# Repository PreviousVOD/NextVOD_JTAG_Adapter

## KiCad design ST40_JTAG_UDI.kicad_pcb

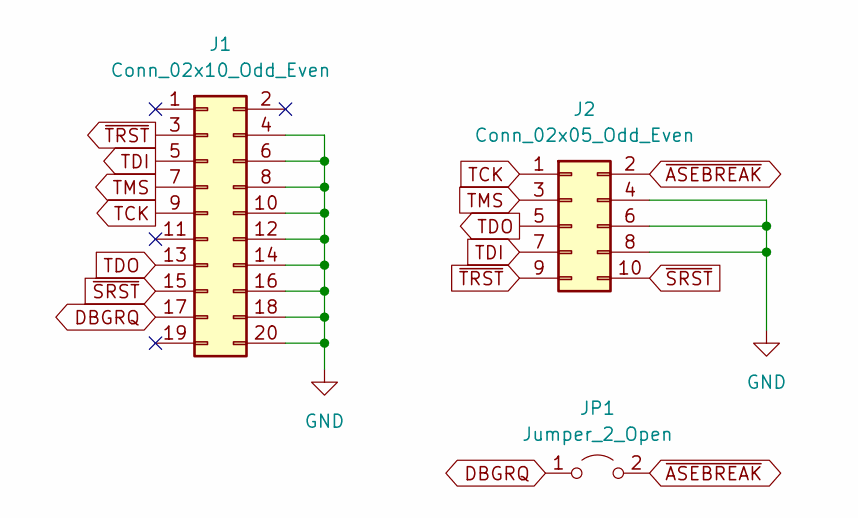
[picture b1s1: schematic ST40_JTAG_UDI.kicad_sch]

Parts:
J1: Conn_02x10_Odd_Even; PinHeader_2x10_P2.54mm_Vertical
J2: Conn_02x05_Odd_Even; PinHeader_2x05_P1.27mm_Vertical
JP1: Jumper_2_Open; SolderJumper-2_P1.3mm_Open_TrianglePad1.0x1.5mm

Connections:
DBGRQ: J1.17, JP1.1 (A)
GND: J1.4, J1.6, J1.8, J1.10, J1.12, J1.14, J1.16, J1.18, J1.20, J2.4, J2.6, J2.8
TCK: J1.9, J2.1
TDI: J1.5, J2.7
TDO: J1.13, J2.5
TMS: J1.7, J2.3
~ASEBREAK: J2.2, JP1.2 (B)
~SRST: J1.15, J2.10
~TRST: J1.3, J2.9

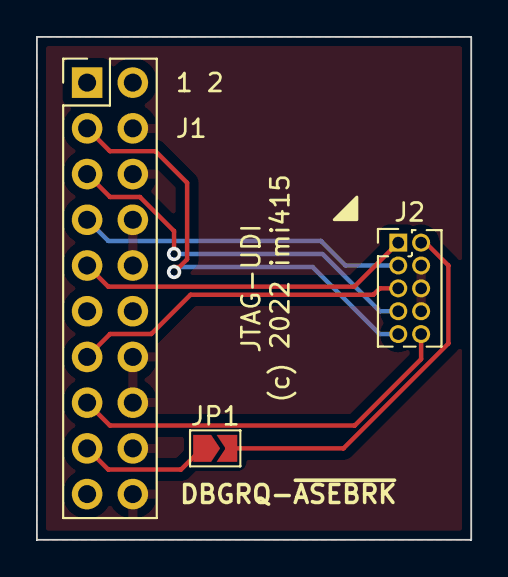
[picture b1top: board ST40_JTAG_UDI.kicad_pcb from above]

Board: 2 copper layers, 24.1 x 27.9 mm, 3 parts (0 on the bottom side), 9 nets.

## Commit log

2022-08-13 Initial Revision A0.
2022-08-13 Added .gitignore and LICENSE.

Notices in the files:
ST40_JTAG_UDI.kicad_pcb:
(c) 2022 imi415
